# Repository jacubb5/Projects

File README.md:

========== Repository Description ==========

This repository contains documentation and technical summaries for projects I have completed or am actively developing during my time at Worcester Polytechnic Institute. These projects span areas such as electronics, embedded systems, mechanical design, and robotics, and are intended to demonstrate both my engineering process and the final results.

Each project folder includes a description of the problem being solved, the approach and design decisions that were made, and what I learned from the process. Some entries are still being documented in more detail, but all represent real work that was built, tested, and iterated on.

If you are reviewing this repository from my resume or portfolio and would like additional technical details, design files, or context for a specific project, feel free to contact me at jacubb5@outlook.com. I am always happy to discuss my work.

Thank you for taking the time to look through my projects.

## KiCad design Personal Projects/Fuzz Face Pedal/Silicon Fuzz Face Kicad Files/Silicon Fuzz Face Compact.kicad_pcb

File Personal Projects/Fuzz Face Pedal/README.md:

Fuzz Face Guitar Pedal

========== Project Description ==========

This project was a Christmas gift for my father, who wanted a Jimi Hendrix–style Fuzz Face guitar pedal. After recently learning PCB design, I realized this would be a good opportunity to design and build a complete electronics product from scratch rather than assembling a kit or copying an existing board.

Beyond recreating a classic pedal, my primary goal was to become self-sufficient in the entire hardware development process. This included schematic design, PCB layout, component sourcing, surface-mount assembly, debugging, enclosure design, and final system integration. The project ended up being significantly more educational than expected and became one of my most hands-on learning experiences in electronics engineering.

Start Date: 11/15/25

End Date: 12/24/25

Last Edited: 1/8/2026

========== Research and Initial Design ==========

At the start of the project, I researched whether building a Fuzz Face pedal was feasible at my skill level. While the circuit itself is relatively simple, it is highly sensitive to component selection, particularly transistor gain. I relied on three primary references throughout the project: a technical breakdown of the Fuzz Face circuit, a silicon Fuzz Face build guide, and an article explaining BJT gain and beta.

Using these resources, I selected the “Fuzz Face with Roger Mayer / Jimi Hendrix mods” schematic as a starting point and recreated it in KiCad to familiarize myself with the circuit and prepare for PCB layout. While comparing multiple schematics, I noticed inconsistencies in component orientation and transistor polarity. Rather than copying a single design, I spent time understanding why these differences existed, which became important later when adapting the circuit.

Fuzz Face With "Jimi Hendrix" Mods Schematic

Schematic Recreated in KiCad

========== Transistor Selection and Circuit Adaptation ==========

One of the most important discoveries during this project was how critical transistor gain (hFE) is to the sound of a Fuzz Face pedal. The target gains were approximately 90 hFE for the first transistor and 140 hFE for the second. Original Hendrix pedals used PNP germanium transistors, which are expensive, difficult to source consistently, and often sold individually after being manually tested.

To keep the project affordable and practical, I chose to redesign the circuit using NPN silicon transistors. This required fully inverting the circuit topology and reversing component orientation, rather than simply swapping parts. Understanding current flow, biasing, and polarity was essential to making this change correctly.

While testing transistors, I learned that bulk transistor tapes typically come from the same manufacturing batch and therefore have very similar gain values. This made it difficult to achieve the mismatched gains required for the circuit. I ultimately sourced transistors from mixed batches and measured them manually to select appropriate pairs.

========== PCB Design and Manufacturing ==========

The PCB was designed in KiCad with an emphasis on compactness. I initially planned to mount the audio jacks and battery directly on the PCB, but mechanical clearance issues and footprint limitations made this impractical. I eventually transitioned to a wired design paired with a custom enclosure.

The board used surface-mount components with hand-solderable footprints. Parts were sourced primarily from Digi-Key, and the PCB was fabricated by JLCPCB. Several design iterations were required due to footprint mismatches and underestimated component sizes, which reinforced the importance of selecting exact parts before committing to a layout.

PCB Designed in KiCad

PCB Rendered in KiCad

Digikey Bill of Materials

========== Assembly and Early Testing ==========

Before leaving campus for winter break, I soldered all PCB components using lab equipment. Due to time constraints, I did not fully test the circuit before leaving, which later became a major lesson learned. At the time, visual inspection suggested the board was assembled correctly, but this proved to be unreliable without proper electrical verification.

========== Debugging, Prototyping, and Enclosure Design ==========

Once home for winter break, I tested the pedal with an electric guitar and amplifier and found that it did not function as expected. I began debugging using a multimeter, oscilloscope, and waveform generator. This process revealed several issues, including incomplete solder joints, incorrect audio jack wiring, and the difficulty of probing surface-mount components.

In parallel, I designed a custom enclosure modeled after a Fuzz Face Mini pedal. Due to limited published dimensions, I worked from reference images and estimated measurements. I imported manufacturer models of the jacks and potentiometers to verify fit, printed the enclosure in PLA, and finished it with primer and paint to match the appearance of classic pedals.

Pedal Assembly in Onshape

3D Printed Enclosure with Primer

Despite extensive debugging, it became unclear whether the remaining issues were caused by individual components, soldering quality, or the PCB design itself. To isolate the problem, I rebuilt the circuit using through-hole components on a breadboard. The circuit worked immediately, confirming that the schematic was correct and that the issues were related to implementation rather than design.

Circuit Testing with Breadboard

========== Final Implementation and Testing ==========

After validating the circuit on a breadboard, I transferred the design to a protoboard that could fit inside the enclosure. I carefully recreated the circuit, checked continuity and resistance across all connections, and resolved several soldering issues. Once completed, the circuit was significantly more stable than the breadboard version and produced consistent output without noise when components were moved.
I performed extended testing using a guitar and amplifier, verifying the behavior of the volume, fuzz, and custom modification potentiometer. The final assembly was then completed and prepared for gifting.

Final Protoboard Circuit

========== Results ==========

A commercially available Fuzz Face pedal costs approximately $180, while this build cost around $75. The cost was higher than necessary due to replacement parts and redesigns, but those expenses were a direct result of learning through iteration. With the experience gained from this project, I am confident that I could recreate a similar pedal more efficiently and at a lower cost.

The final sound closely matched the classic Hendrix-style fuzz I was aiming for. The added modification control provided additional tonal flexibility, giving the pedal a distinct character beyond the original design. The enclosure fit well, and the overall build quality exceeded my initial expectations. Most importantly, my father was very happy with the final result.

3D Printed Enclosure Fully Painted (Top View)

3D Printed Enclosure Fully Painted (Rear View)

========== Engineering Takeaways ==========

This project was my first experience building a complete electronic system from schematic to physical product, and it fundamentally changed how I think about hardware design. I learned that a working schematic is only a small part of a successful system. Component selection, footprint accuracy, solderability, mechanical constraints, and signal integrity all play equally important roles. Small mismatches between what exists in CAD and what arrives in the mail can easily cause a design to fail if they are not carefully planned for.

Debugging the pedal forced me to develop a structured approach to fault isolation. When the PCB did not work, I had to determine whether the issue came from the circuit design, the PCB layout, the soldering quality, or individual components. Rebuilding the same circuit on a breadboard allowed me to separate the electrical design from the physical implementation, which is a critical debugging technique in robotics and embedded systems. This process taught me how to systematically reduce uncertainty rather than randomly changing parts and hoping the problem disappears.

I gained practical experience working with analog electronics, particularly transistor biasing and gain matching. The Fuzz Face is extremely sensitive to transistor parameters, which meant I could not treat parts as interchangeable. Measuring hFE, understanding manufacturing batches, and selecting matched transistor pairs taught me how real components differ from their idealized datasheet values. This is directly relevant to any robotics system that relies on sensors, amplifiers, or power electronics, where component variation can significantly affect behavior.

The project also highlighted the importance of feedback between electrical and mechanical design. Decisions about PCB size, connector placement, and component orientation affected how the enclosure could be designed and how reliable the final product felt. Designing the enclosure after the PCB rather than before created unnecessary constraints, which reinforced the importance of co-designing mechanical and electrical systems in parallel.

Using surface-mount components gave me experience with manufacturing-scale electronics, but also revealed the tradeoffs between compactness and serviceability. SMDs made the board smaller and more professional-looking, but they were much harder to probe, rework, and debug than through-hole parts. This taught me how to choose different technologies depending on whether the goal is rapid prototyping, testing, or final production.

Finally, the project taught me how to manage iteration under real constraints. Time, cost, part availability, and tool access all influenced the decisions I had to make. Instead of aiming for a perfect first build, I learned to converge on a working solution through testing, failure, and incremental improvement. That mindset is central to building reliable robotic and electronic systems in the real world.

========== Summary ==========

This project was more than a guitar pedal build. It was a complete hardware development cycle involving electrical design, manufacturing, mechanical integration, debugging, and iteration under time constraints. The experience directly improved my confidence and competence in designing, building, and troubleshooting real-world electronic systems, and it closely reflects the type of multidisciplinary problem solving required in robotics engineering.

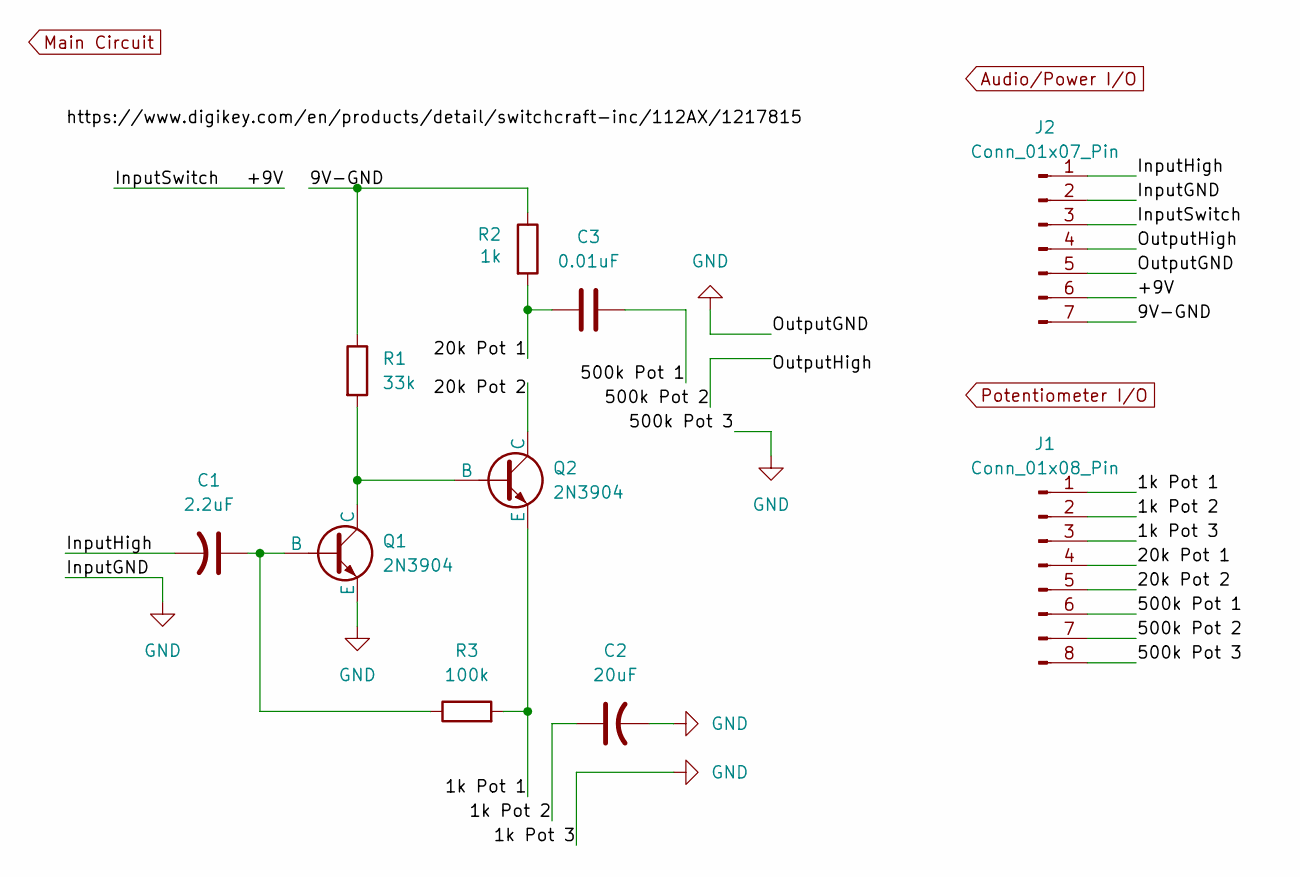
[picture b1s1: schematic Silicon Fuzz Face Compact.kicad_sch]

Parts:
C1: 2.2uF; C_0603_1608Metric_Pad1.08x0.95mm_HandSolder
C2: 20uF; C_0603_1608Metric_Pad1.08x0.95mm_HandSolder
C3: 0.01uF; C_0603_1608Metric_Pad1.08x0.95mm_HandSolder
J1: Conn_01x08_Pin; PinHeader_1x08_P2.54mm_Vertical
J2: Conn_01x07_Pin; PinHeader_1x07_P2.54mm_Vertical
Q1, Q2: 2N3904; TO-92_HandSolder
R1: 33k; R_0603_1608Metric_Pad0.98x0.95mm_HandSolder
R2: 1k; R_0603_1608Metric_Pad0.98x0.95mm_HandSolder
R3: 100k; R_0603_1608Metric_Pad0.98x0.95mm_HandSolder

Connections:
/1k Pot 1: J1.1, Q2.3 (E), R3.2
/1k Pot 2: C2.1, J1.2
/9V-GND: J2.7, R1.1, R2.1
/20k Pot 1: C3.1, J1.4, R2.2
/20k Pot 2: J1.5, Q2.1 (C)
/500k Pot 1: C3.2, J1.6
/500k Pot 2: J1.7, J2.4
/+9V: J2.3, J2.6
/InputHigh: C1.2, J2.1
GND: C2.2, J1.3, J1.8, J2.2, J2.5, Q1.3 (E)
unnamed: C1.1, Q1.2 (B), R3.1
unnamed: Q1.1 (C), Q2.2 (B), R1.2

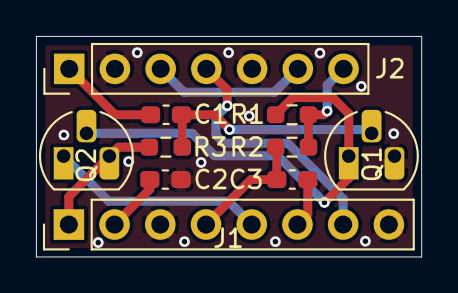
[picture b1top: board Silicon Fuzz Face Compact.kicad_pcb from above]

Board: 2 copper layers, 21.4 x 12.2 mm, 10 parts (0 on the bottom side), 12 nets.

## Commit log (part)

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2026-01-06 Added Folders
2026-01-11 Added Fuzz Face and HPRC Projects
2026-01-11 Fixed HPRC Formatting
2026-01-11 Fixed Fuzz Face Formatting
2026-01-11 Uploaded Fuzz Face Kicad Files
2026-01-12 Added RBE 2002 Details
2026-01-12 Added Header Readme and RBE 2002 Lab Readme
2026-01-12 Fixed HPRC Tracker Readme Spacing Issue
2026-01-16 Added Photo Gallery to Fuzz Face Readme
2026-01-16 Integrated Fuzz Face Photo Gallery with Body Text
2026-01-16 Added Photos to Tracking Antenna
